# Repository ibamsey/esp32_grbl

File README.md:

# esp32_grbl
CNC Drive for ESP32

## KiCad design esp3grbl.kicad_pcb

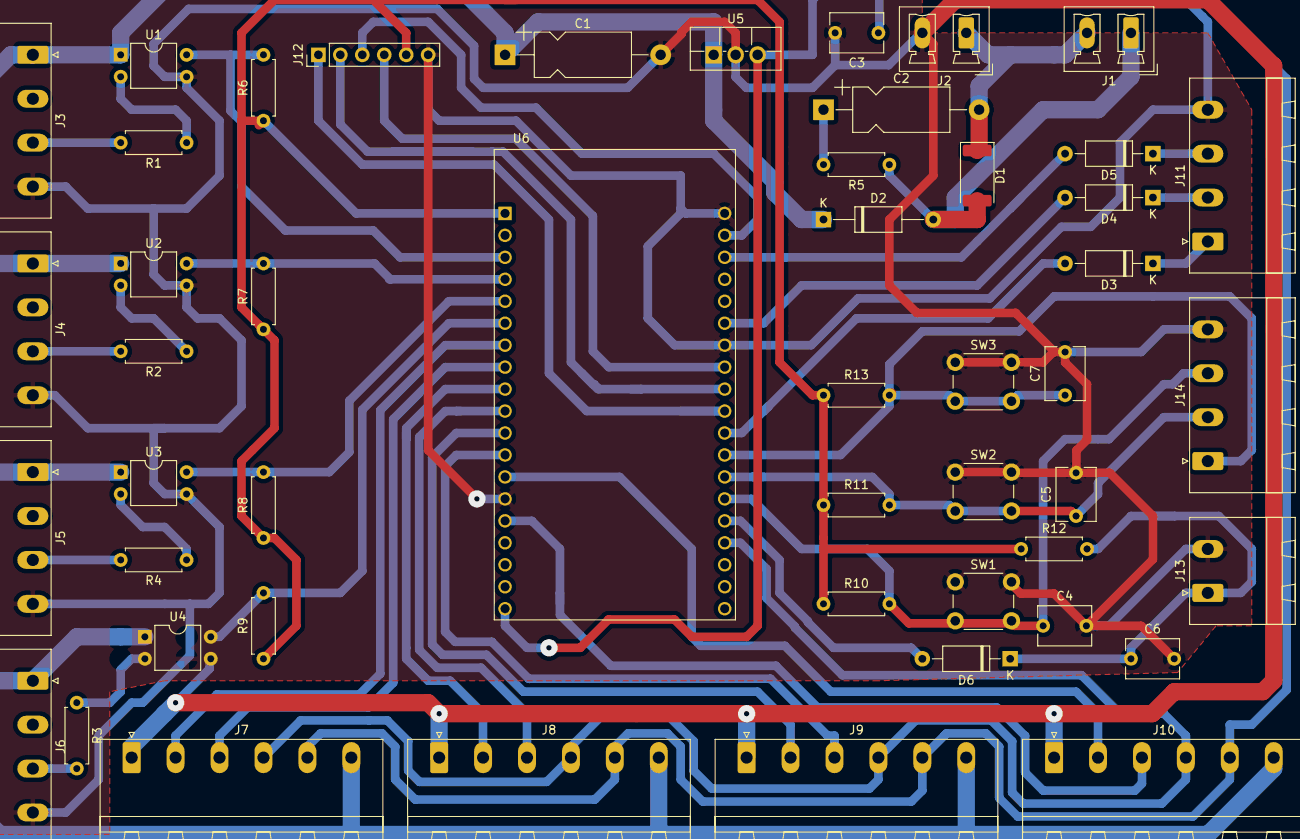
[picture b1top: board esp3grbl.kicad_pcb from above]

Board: 2 copper layers, 49 parts (0 on the bottom side), 43 nets.

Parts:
C1: 0.33uF; CP_Axial_L11.0mm_D5.0mm_P18.00mm_Horizontal
C2: 1uF; CP_Axial_L11.0mm_D5.0mm_P18.00mm_Horizontal
C3, C4, C5, C6, C7: 0.1uF; C_Disc_D6.0mm_W4.4mm_P5.00mm
D1: D_TVS; D_2512_6332Metric
D2: D_Schottky; D_A-405_P12.70mm_Horizontal
D3, D4, D5, D6: D; D_A-405_P10.16mm_Horizontal
J1: Emergency Stop; PhoenixContact_MCV_1,5_2-G-5.08_1x02_P5.08mm_Vertical
J2: Power Supply; PhoenixContact_MCV_1,5_2-G-5.08_1x02_P5.08mm_Vertical
J3: Y1 Limit; PhoenixContact_MSTBA_2,5_4-G-5,08_1x04_P5.08mm_Horizontal
J4: X Limit; PhoenixContact_MSTBA_2,5_4-G-5,08_1x04_P5.08mm_Horizontal
J5: Y2 Limit; PhoenixContact_MSTBA_2,5_4-G-5,08_1x04_P5.08mm_Horizontal
J6: Z limit; PhoenixContact_MSTBA_2,5_4-G-5,08_1x04_P5.08mm_Horizontal
J7: Z axis; PhoenixContact_MSTBA_2,5_6-G-5,08_1x06_P5.08mm_Horizontal
J8: Y1-Axis; PhoenixContact_MSTBA_2,5_6-G-5,08_1x06_P5.08mm_Horizontal
J9: Y2 - Axis; PhoenixContact_MSTBA_2,5_6-G-5,08_1x06_P5.08mm_Horizontal
J10: x - axis; PhoenixContact_MSTBA_2,5_6-G-5,08_1x06_P5.08mm_Horizontal
J11: Outputs; PhoenixContact_MSTBA_2,5_4-G-5,08_1x04_P5.08mm_Horizontal
J12: Micro_SD_Card_Adater; PinHeader_1x06_P2.54mm_Vertical
J13: Probe; PhoenixContact_MSTBA_2,5_2-G-5,08_1x02_P5.08mm_Horizontal
J14: Buttons; PhoenixContact_MSTBA_2,5_4-G-5,08_1x04_P5.08mm_Horizontal
R1, R2, R3, R4: 1k; R_Axial_DIN0207_L6.3mm_D2.5mm_P7.62mm_Horizontal
R5: R163; R_Axial_DIN0207_L6.3mm_D2.5mm_P7.62mm_Horizontal
R6, R7, R8, R9, R10, R11, R12, R13: 10k; R_Axial_DIN0207_L6.3mm_D2.5mm_P7.62mm_Horizontal
SW1: Canel; SW_PUSH_6mm
SW2: Play; SW_PUSH_6mm
SW3: SW_Push; SW_PUSH_6mm
U1, U2, U3, U4: PC817; DIP-4_W7.62mm
U5: L7805; TO-220F-3_Vertical
U6: ESP32-DEVKITC-32D; MODULE_ESP32-DEVKITC-32D

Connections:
+3V3: J12.5, R6.1, R7.1, R8.1, R9.1, R10.1, R11.1, R12.1, R13.1, U6.1
+5V: C3.1, J7.5, J8.5, J9.5, J10.5, U5.3, U6.19
+12V: C1.1, D2.1, J3.1, J4.1, J5.1, J6.1, J7.6, J8.6, J9.6, J10.6, U1.1, U2.1, U3.1, U4.1, U5.1
/12V: C2.2, D1.1, J1.2, J2.1
/12VDC: D1.2, D2.2, J1.1, R5.1
/CS: J12.1, U6.29
/GPIO_NUM_12: J10.2, U6.13
/GPIO_NUM_13: J10.3, U6.15
/GPIO_NUM_14: J9.3, U6.12
/GPIO_NUM_25: J8.2, U6.9
/GPIO_NUM_26: J8.3, U6.10
/GPIO_NUM_27: J9.2, U6.11
/GPIO_NUM_32: J7.2, U6.7
/GPIO_NUM_33: J7.3, U6.8
/GPIO_NUM_34: R8.2, U3.4, U6.5
/GPIO_NUM_35: R9.2, U4.4, U6.6
/GPIO_NUM_36: R6.2, U1.4, U6.3
/GPIO_NUM_39: R7.2, U2.4, U6.4
/MISO: J12.4, U6.27
/MOSI: J12.3, U6.21
/SCK: J12.2, U6.28
/x-enable: J7.4, J8.4, J9.4, J10.4, U6.35
Aux: D5.2, U6.22
Cancel: C7.1, J14.1, R13.2, SW3.2, U6.31
Coolant: D4.2, U6.25
GND: C1.2, C3.2, C4.2, C5.2, C6.2, C7.2, J2.2, J3.4, J4.4, J5.4, J6.4, J7.1, J8.1, J9.1, J10.1, J11.4, J12.6, J13.2, J14.4, SW1.1, SW2.1, SW3.1, U1.3, U2.3, U3.3, U4.3, U5.2, U6.14, U6.20, U6.26
unnamed: C2.1, R5.2
unnamed: C6.1, D6.1, J13.1, R12.2
unnamed: D3.1, J11.1
unnamed: D4.1, J11.2
unnamed: D5.1, J11.3
unnamed: J3.3, R1.2
unnamed: J4.3, R2.2
unnamed: J5.3, R4.2
unnamed: J6.3, R3.2
unnamed: R1.1, U1.2
unnamed: R2.1, U2.2
unnamed: R3.1, U4.2
unnamed: R4.1, U3.2
Pause: C4.1, J14.3, R10.2, SW1.2, U6.33
Play: C5.1, J14.2, R11.2, SW2.2, U6.32
Probe: D6.2, U6.34
Spindle_PWM: D3.2, U6.30

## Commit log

2021-11-26 added
2021-12-29 Refine layout and screen mask
